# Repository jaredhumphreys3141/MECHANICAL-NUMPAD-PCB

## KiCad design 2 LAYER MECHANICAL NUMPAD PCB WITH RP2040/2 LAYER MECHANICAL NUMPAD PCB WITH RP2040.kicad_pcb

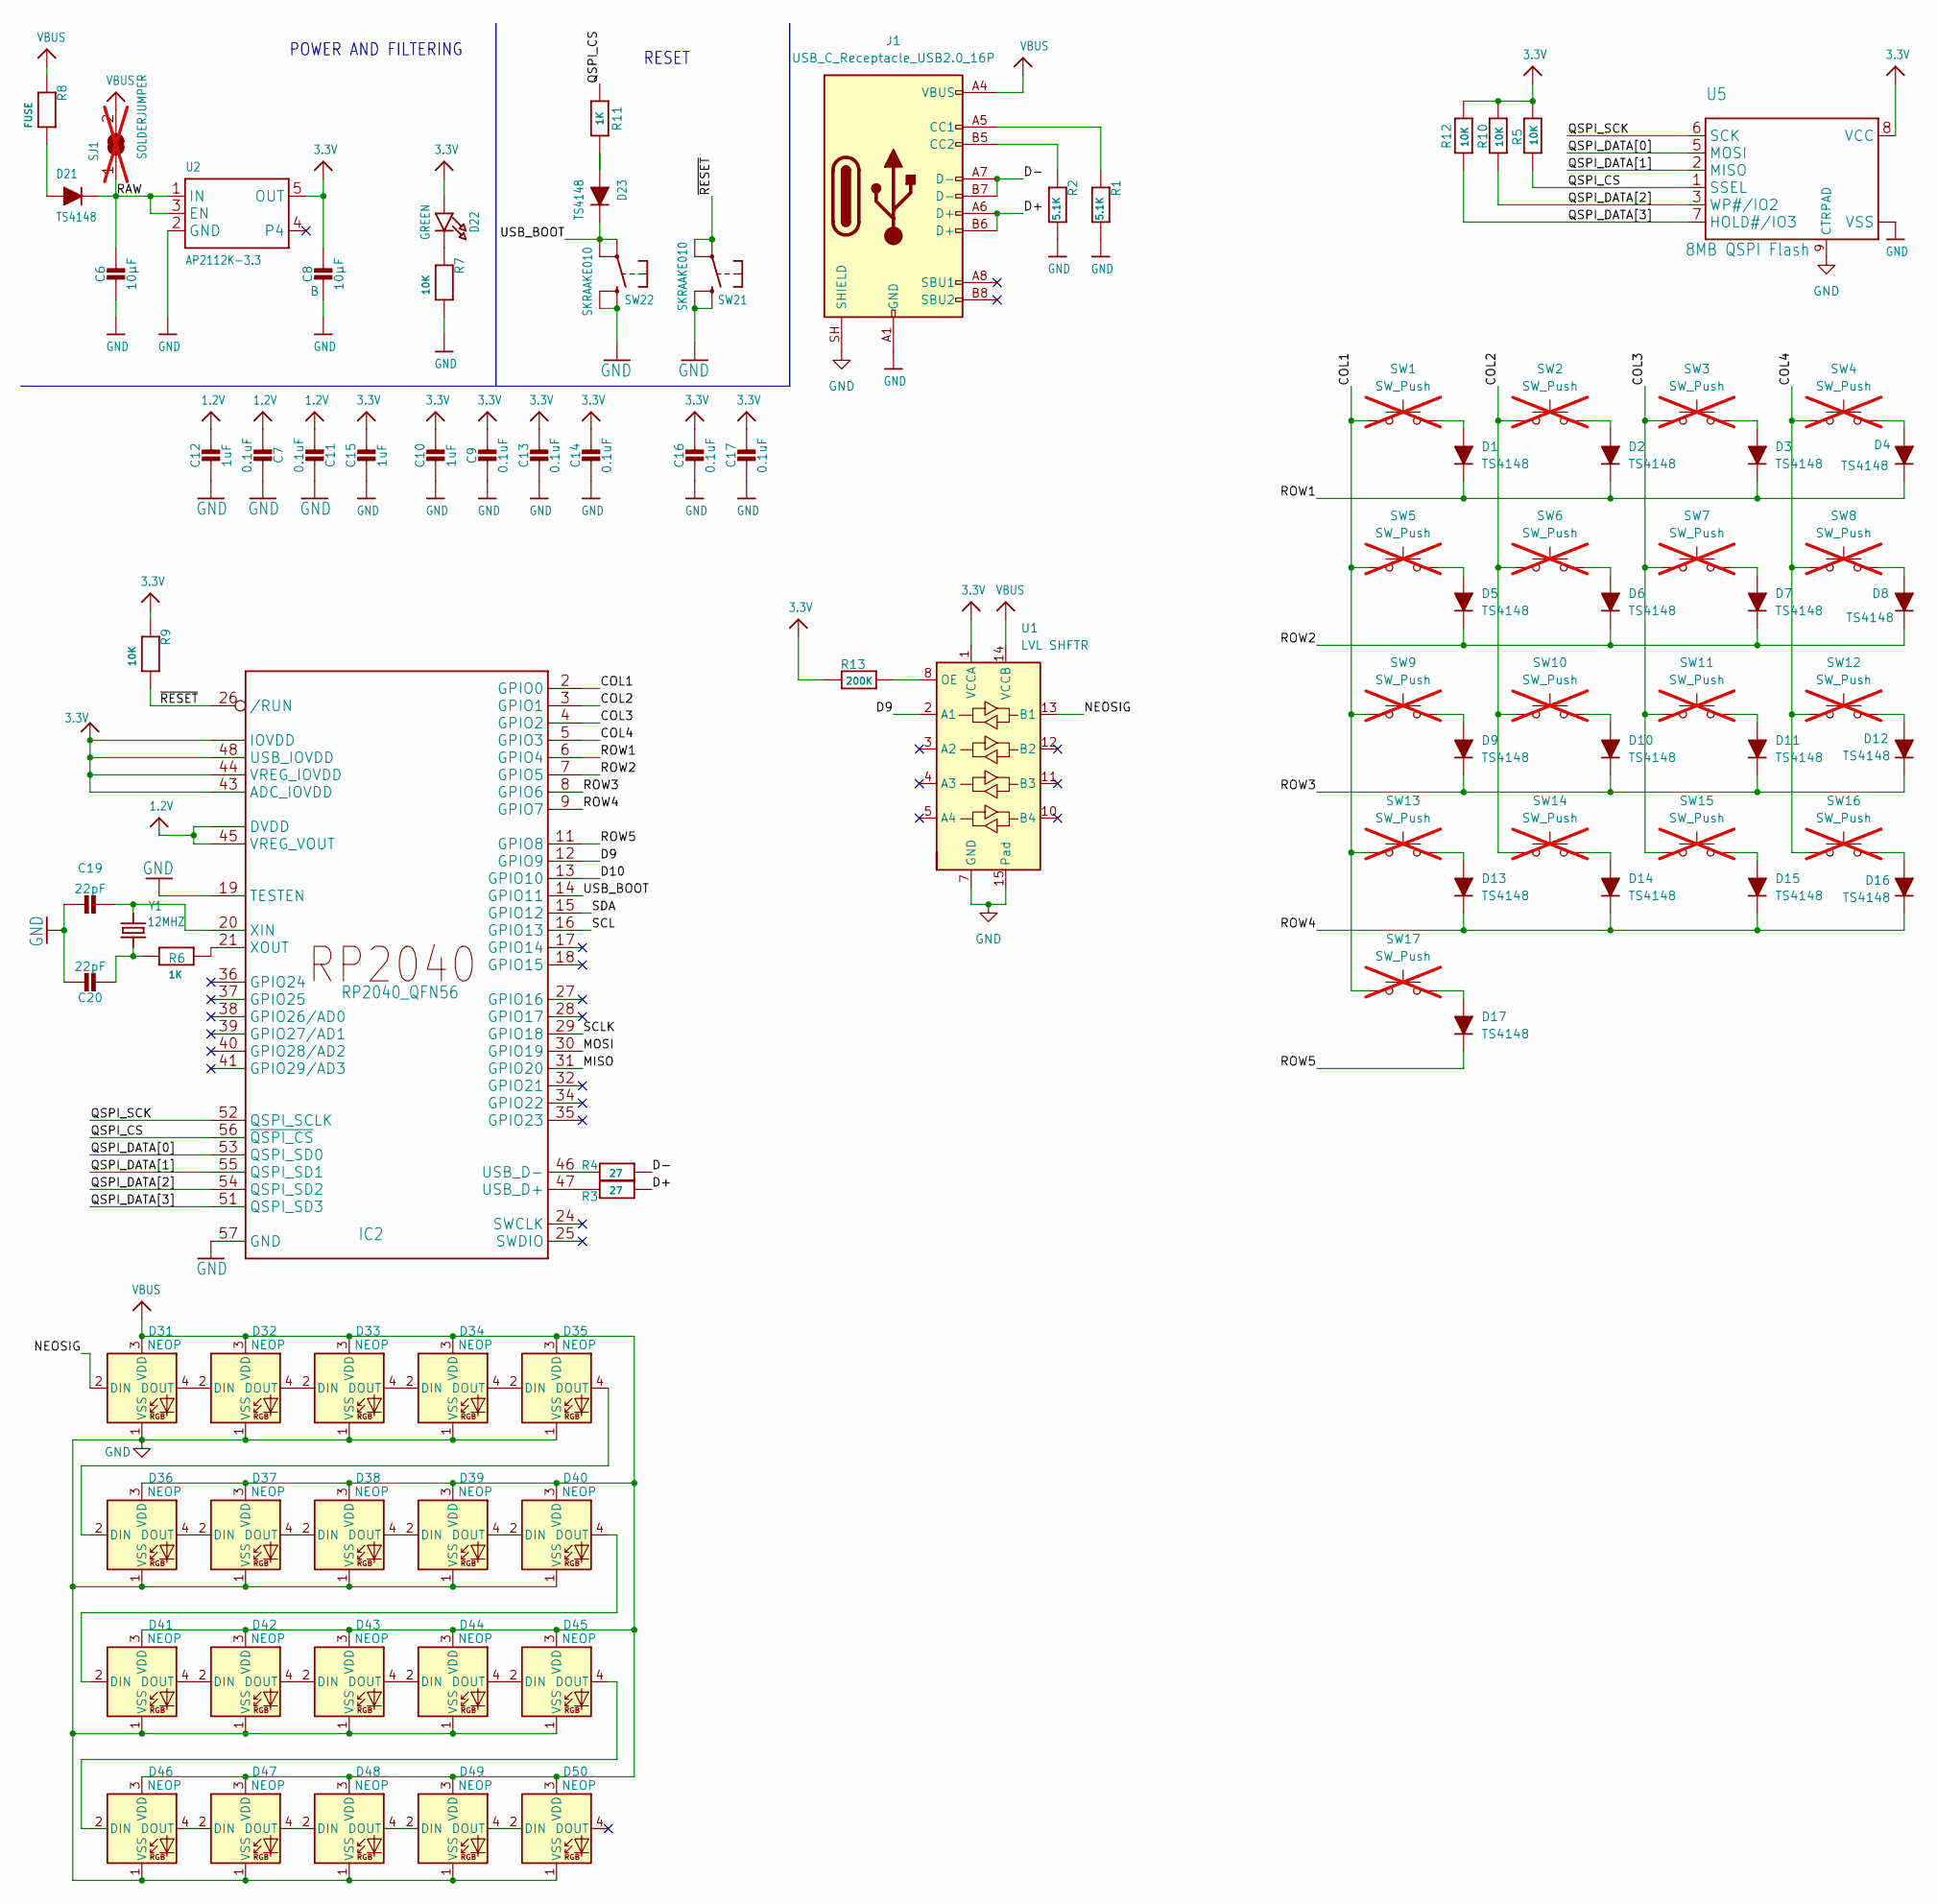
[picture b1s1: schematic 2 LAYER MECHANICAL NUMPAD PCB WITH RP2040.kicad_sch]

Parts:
C6, C8: 10µF; C_0603_1608Metric
C7, C9, C11, C13, C14, C16, C17: 0.1uF; C_0603_1608Metric
C10, C12, C15: 1uF; C_0603_1608Metric
C19, C20: 22pF; C_0603_1608Metric
D1, D2, D3, D4, D5, D6, D7, D8, D9, D10, D11, D12, D13, D14, D15, D16, D17, D21, D23: TS4148; D_0805_2012Metric
D22: GREEN; LED_0603_1608Metric_Green
D31, D32, D33, D34, D35, D36, D37, D38, D39, D40, D41, D42, D43, D44, D45, D46, D47, D48, D49, D50: NEOP; LED_SK6812MINI-E_3.2x2.8mm_P1.5mm_ReverseMount
IC2: RP2040_QFN56; QFN-56-1EP_7x7mm_P0.4mm_EP3.2x3.2mm
J1: USB_C_Receptacle_USB2.0_16P; USB_C_Receptacle_GCT_USB4105-xx-A_16P_TopMnt_Horizontal
R1, R2: 5.1K; R_0603_1608Metric
R3, R4: 27; R_0603_1608Metric
R5, R7, R9, R10, R12: 10K; R_0603_1608Metric
R6, R11: 1K; R_0603_1608Metric
R8: FUSE; Fuse_0603_1608Metric
R13: 200K; R_0603_1608Metric
SJ1: SOLDERJUMPER; SolderJumper-2_P1.3mm_Open_Pad1.0x1.5mm; not fitted
SW1, SW2, SW3, SW4, SW5, SW6, SW7, SW8, SW9, SW10, SW11, SW12, SW13, SW14, SW15, SW16, SW17: SW_Push; SW_Hotswap_Kailh_MX_1.00u; not fitted
SW21, SW22: SKRAAKE010; SW4_SKRAAKE010_ALPS
U1: LVL SHFTR; Texas_S-PVQFN-N14
U2: AP2112K-3.3; SOT23-5
U5: 8MB QSPI Flash; USON-8_3x2mm-SkinnyCenterPad
Y1: 12MHZ; Crystal_SMD_3215-2Pin_3.2x1.5mm

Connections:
1.2V: C7.2, C11.2, C12.1, IC2.23 (DVDD), IC2.45 (VREG_VOUT), IC2.50 (DVDD)
3.3V: C8.1, C9.1, C10.1, C13.1, C14.1, C15.1, C16.1, C17.1, D22.1 (A), IC2.1 (IOVDD), IC2.10 (IOVDD), IC2.22 (IOVDD), IC2.33 (IOVDD), IC2.42 (IOVDD), IC2.43 (ADC_IOVDD), IC2.44 (VREG_IOVDD), IC2.48 (USB_IOVDD), IC2.49 (IOVDD), R5.2, R9.1, R10.2, R12.2, R13.1, U1.1 (VCCA), U2.5 (OUT), U5.8 (VCC)
/COL1: IC2.2 (GPIO0), SW1.1, SW5.1, SW9.1, SW13.1, SW17.1
/COL2: IC2.3 (GPIO1), SW2.1, SW6.1, SW10.1, SW14.1
/COL3: IC2.4 (GPIO2), SW3.1, SW7.1, SW11.1, SW15.1
/COL4: IC2.5 (GPIO3), SW4.1, SW8.1, SW12.1, SW16.1
/D9: IC2.12 (GPIO9), U1.2 (A1)
/D10: IC2.13 (GPIO10)
/D+: J1.A6 (D+), J1.B6 (D+), R3.2
/D-: J1.A7 (D-), J1.B7 (D-), R4.2
/MISO: IC2.31 (GPIO20)
/MOSI: IC2.30 (GPIO19)
/NEOSIG: D31.2 (DIN), U1.13 (B1)
/QSPI_CS: IC2.56 (~QSPI_CS), R5.1, R11.1, U5.1 (SSEL)
/QSPI_DATA[0]: IC2.53 (QSPI_SD0), U5.5 (MOSI)
/QSPI_DATA[1]: IC2.55 (QSPI_SD1), U5.2 (MISO)
/QSPI_DATA[2]: IC2.54 (QSPI_SD2), R10.1, U5.3 (WP#/IO2)
/QSPI_DATA[3]: IC2.51 (QSPI_SD3), R12.1, U5.7 (HOLD#/IO3)
/QSPI_SCK: IC2.52 (QSPI_SCLK), U5.6 (SCK)
/RAW: C6.1, D21.1 (K), SJ1.1, U2.1 (IN), U2.3 (EN)
/ROW1: D1.1 (K), D2.1 (K), D3.1 (K), D4.1 (K), IC2.6 (GPIO4)
/ROW2: D5.1 (K), D6.1 (K), D7.1 (K), D8.1 (K), IC2.7 (GPIO5)
/ROW3: D9.1 (K), D10.1 (K), D11.1 (K), D12.1 (K), IC2.8 (GPIO6)
/ROW4: D13.1 (K), D14.1 (K), D15.1 (K), D16.1 (K), IC2.9 (GPIO7)
/ROW5: D17.1 (K), IC2.11 (GPIO8)
/SCL: IC2.16 (GPIO13)
/SCLK: IC2.29 (GPIO18)
/SDA: IC2.15 (GPIO12)
/USB_BOOT: D23.1 (K), IC2.14 (GPIO11), SW22.1, SW22.3 (P1)
/~RESET: IC2.26 (/RUN), R9.2, SW21.1, SW21.3 (P1)
GND: C6.2, C7.1, C8.2, C9.2, C10.2, C11.1, C12.2, C13.2, C14.2, C15.2, C16.2, C17.2, C19.1, C20.1, D31.1 (VSS), D32.1 (VSS), D33.1 (VSS), D34.1 (VSS), D35.1 (VSS), D36.1 (VSS), D37.1 (VSS), D38.1 (VSS), D39.1 (VSS), D40.1 (VSS), D41.1 (VSS), D42.1 (VSS), D43.1 (VSS), D44.1 (VSS), D45.1 (VSS), D46.1 (VSS), D47.1 (VSS), D48.1 (VSS), D49.1 (VSS), D50.1 (VSS), IC2.19 (TESTEN), IC2.57 (GND), J1.A1 (GND), J1.A12 (GND), J1.B1 (GND), J1.B12 (GND), J1.SH (SHIELD), R1.2, R2.2, R7.2, SW21.2 (S), SW21.4 (S1), SW22.2 (S), SW22.4 (S1), U1.7 (GND), U1.15 (Pad), U2.2 (GND), U5.4 (VSS), U5.9 (CTRPAD)
unnamed: C20.2, R6.1, Y1.1
unnamed: D1.2 (A), SW1.2
unnamed: D2.2 (A), SW2.2
unnamed: D3.2 (A), SW3.2
unnamed: D4.2 (A), SW4.2
unnamed: D5.2 (A), SW5.2
unnamed: D6.2 (A), SW6.2
unnamed: D7.2 (A), SW7.2
unnamed: D8.2 (A), SW8.2
unnamed: D9.2 (A), SW9.2
unnamed: D10.2 (A), SW10.2
unnamed: D11.2 (A), SW11.2
unnamed: D12.2 (A), SW12.2
unnamed: D13.2 (A), SW13.2
unnamed: D14.2 (A), SW14.2
unnamed: D15.2 (A), SW15.2
unnamed: D16.2 (A), SW16.2
unnamed: D17.2 (A), SW17.2
unnamed: D21.2 (A), R8.2
unnamed: D22.2 (C), R7.1
unnamed: D23.2 (A), R11.2
unnamed: D31.4 (DOUT), D32.2 (DIN)
unnamed: D32.4 (DOUT), D33.2 (DIN)
unnamed: D33.4 (DOUT), D34.2 (DIN)
unnamed: D34.4 (DOUT), D35.2 (DIN)
unnamed: D35.4 (DOUT), D36.2 (DIN)
unnamed: D36.4 (DOUT), D37.2 (DIN)
unnamed: D37.4 (DOUT), D38.2 (DIN)
unnamed: D38.4 (DOUT), D39.2 (DIN)
unnamed: D39.4 (DOUT), D40.2 (DIN)
unnamed: D40.4 (DOUT), D41.2 (DIN)
unnamed: D41.4 (DOUT), D42.2 (DIN)
unnamed: D42.4 (DOUT), D43.2 (DIN)
unnamed: D43.4 (DOUT), D44.2 (DIN)
unnamed: D44.4 (DOUT), D45.2 (DIN)
unnamed: D45.4 (DOUT), D46.2 (DIN)
unnamed: D46.4 (DOUT), D47.2 (DIN)
unnamed: D47.4 (DOUT), D48.2 (DIN)
unnamed: D48.4 (DOUT), D49.2 (DIN)
unnamed: D49.4 (DOUT), D50.2 (DIN)
unnamed: IC2.47 (USB_D+), R3.1
unnamed: IC2.46 (USB_D-), R4.1
unnamed: C19.2, IC2.20 (XIN), Y1.2
unnamed: IC2.21 (XOUT), R6.2
unnamed: J1.A5 (CC1), R1.1
unnamed: J1.B5 (CC2), R2.1
unnamed: R13.2, U1.8 (OE)
VBUS: D31.3 (VDD), D32.3 (VDD), D33.3 (VDD), D34.3 (VDD), D35.3 (VDD), D36.3 (VDD), D37.3 (VDD), D38.3 (VDD), D39.3 (VDD), D40.3 (VDD), D41.3 (VDD), D42.3 (VDD), D43.3 (VDD), D44.3 (VDD), D45.3 (VDD), D46.3 (VDD), D47.3 (VDD), D48.3 (VDD), D49.3 (VDD), D50.3 (VDD), J1.A4 (VBUS), J1.A9 (VBUS), J1.B4 (VBUS), J1.B9 (VBUS), R8.1, SJ1.2, U1.14 (VCCB)

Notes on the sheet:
RESET
POWER AND FILTERING

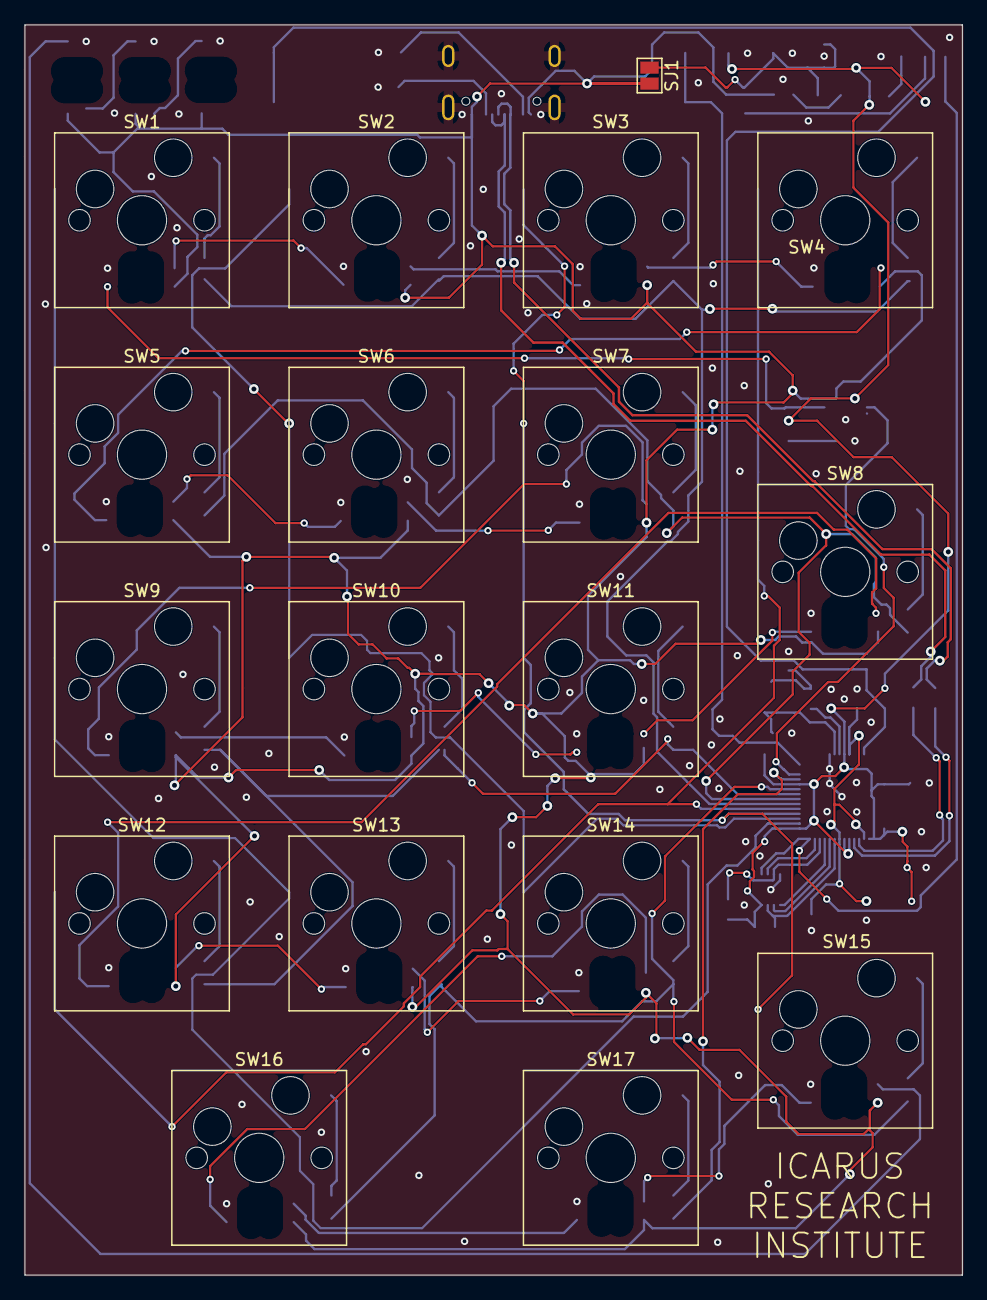
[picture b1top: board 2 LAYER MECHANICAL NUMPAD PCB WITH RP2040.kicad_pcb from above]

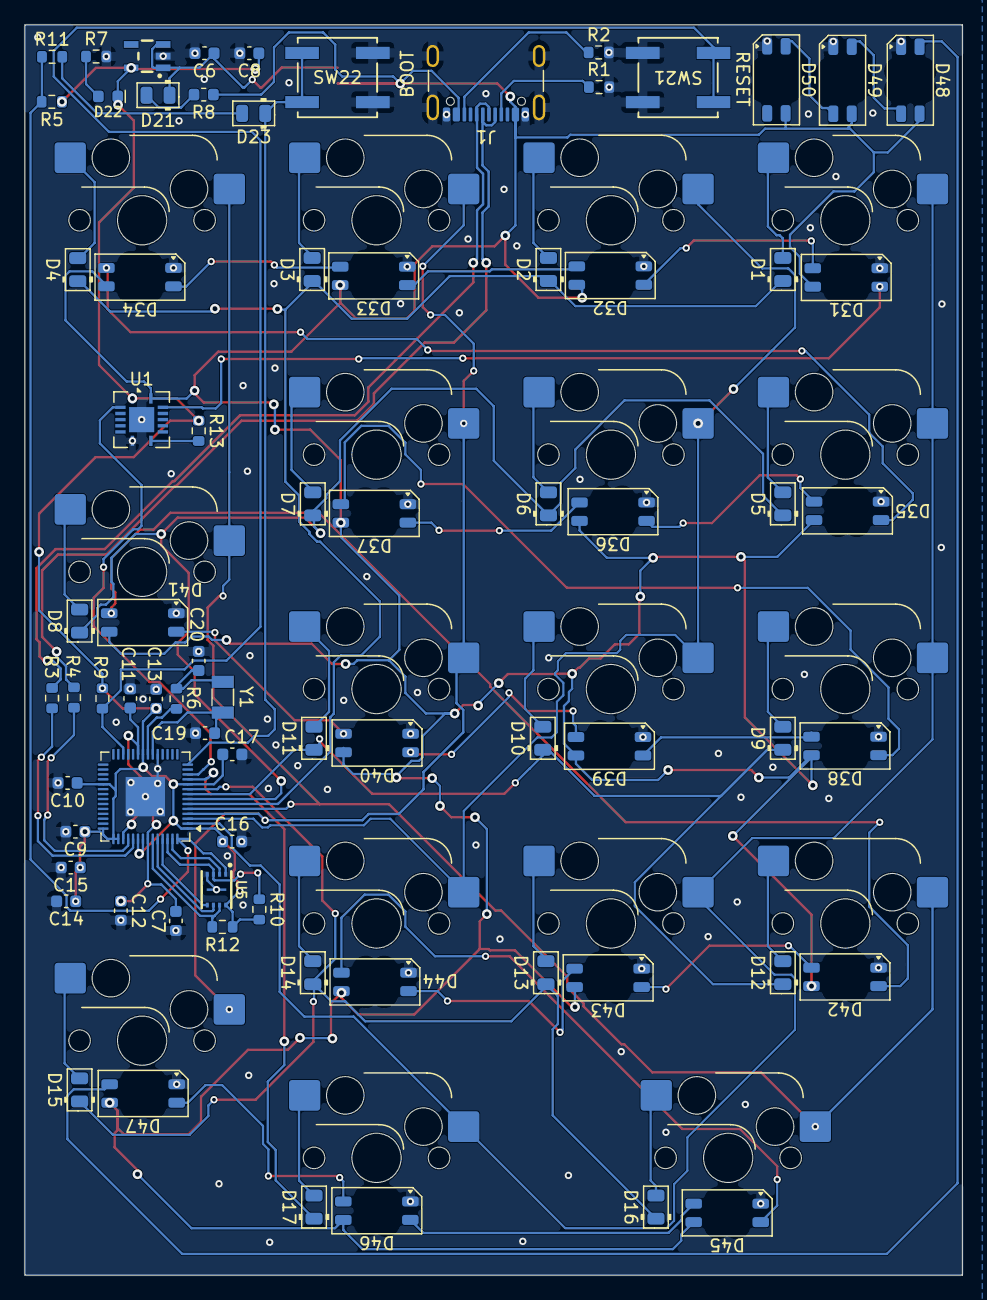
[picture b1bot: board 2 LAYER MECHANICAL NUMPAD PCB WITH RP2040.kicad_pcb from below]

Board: 2 copper layers, 76.2 x 101.6 mm, 93 parts (75 on the bottom side), 73 nets.

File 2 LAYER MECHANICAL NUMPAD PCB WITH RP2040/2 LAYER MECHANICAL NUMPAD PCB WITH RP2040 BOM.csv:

"Id";"Designator";"Footprint";"Quantity";"Designation";"Supplier and ref";
1;"C6, C8";"C_0603_1608Metric";2;"10µF";;;
2;"C7, C9, C11, C13, C14, C16, C17";"C_0603_1608Metric";7;"0.1uF";;;
3;"C10, C12, C15";"C_0603_1608Metric";3;"1uF";;;
4;"C19, C20";"C_0603_1608Metric";2;"22pF";;;
5;"D1, D2, D3, D4, D5, D6, D7, D8, D9, D10, D11, D12, D13, D14, D15, D16, D17, D21, D23";"D_0805_2012Metric";19;"TS4148";;;
6;"D22";"LED_0603_1608Metric_Green";1;"GREEN";;;
7;"D31, D32, D33, D34, D35, D36, D37, D38, D39, D40, D41, D42, D43, D44, D45, D46, D47, D48, D49, D50";"LED_SK6812MINI-E_3.2x2.8mm_P1.5mm_ReverseMount";20;"NEOP";;;
8;"IC2";"QFN-56-1EP_7x7mm_P0.4mm_EP3.2x3.2mm";1;"RP2040_QFN56";;;
9;"J1";"USB_C_Receptacle_GCT_USB4105-xx-A_16P_TopMnt_Horizontal";1;"USB_C_Receptacle_USB2.0_16P";;;
10;"R1, R2";"R_0603_1608Metric";2;"5.1K";;;
11;"R3, R4";"R_0603_1608Metric";2;"27";;;
12;"R5, R7, R9, R10, R12";"R_0603_1608Metric";5;"10K";;;
13;"R6, R11";"R_0603_1608Metric";2;"1K";;;
14;"R8";"Fuse_0603_1608Metric";1;"FUSE";;;
15;"R13";"R_0603_1608Metric";1;"200K";;;
16;"SW21, SW22";"SW4_SKRAAKE010_ALPS";2;"SKRAAKE010";;;
17;"U1";"Texas_S-PVQFN-N14";1;"LVL SHFTR";;;
18;"U2";"SOT23-5";1;"AP2112K-3.3";;;
19;"U5";"USON-8_3x2mm-SkinnyCenterPad";1;"8MB QSPI Flash";;;
20;"Y1";"Crystal_SMD_3215-2Pin_3.2x1.5mm";1;"12MHZ";;;

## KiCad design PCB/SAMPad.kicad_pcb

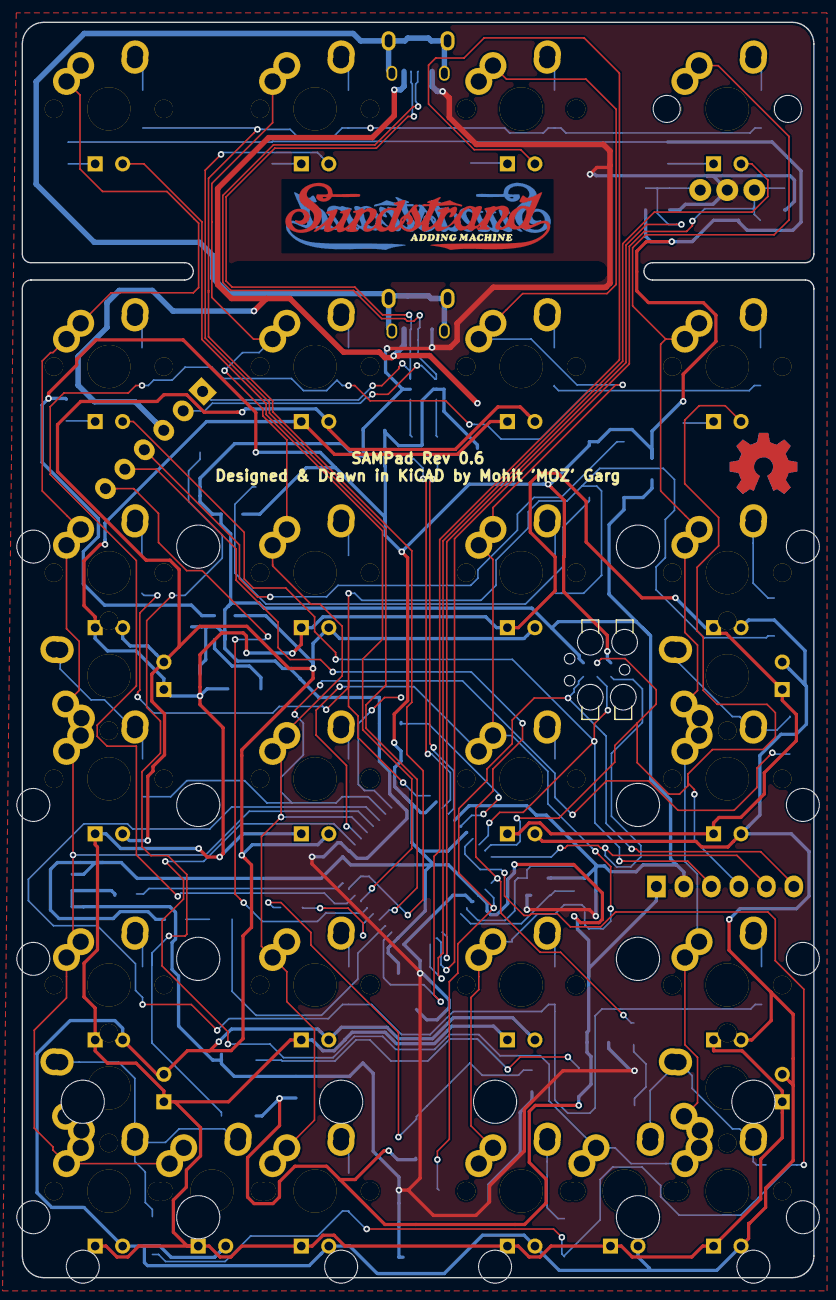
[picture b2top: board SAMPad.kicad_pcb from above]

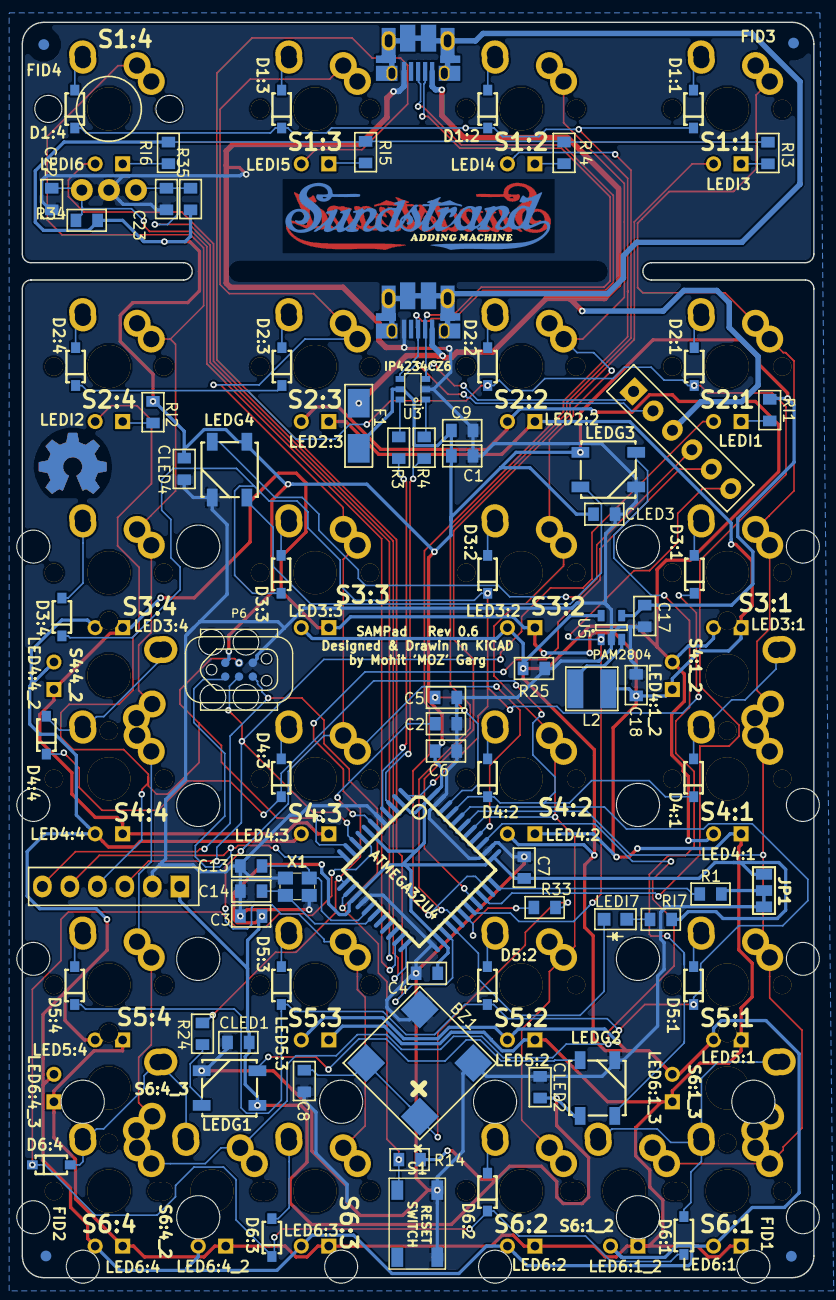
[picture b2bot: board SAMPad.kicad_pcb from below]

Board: 2 copper layers, 73.2 x 116.0 mm, 154 parts (85 on the bottom side), 79 nets.

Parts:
BZ1: BUZZER; BUZZER_SMT
C1, C2, C22, C23: 1uF; SMD_0805
C3, C4, C5, C6, C7, C8: 0.1uF; SMD_0805
C9, C17, C18: 10uF; SMD_0805
C13, C14: 8pF; SMD_0805
CLED1, CLED2, CLED3, CLED4: 0.1 uF; SMD_0805
D1:1, D1:2, D1:3, D1:4, D2:1, D2:2, D2:3, D2:4, D3:1, D3:2, D3:3, D3:4, D4:1, D4:2, D4:3, D4:4, D5:1, D5:2, D5:3, D5:4, D6:1, D6:2, D6:3, D6:4: DIODE; SOD123-DIODE
F1: PTC FUSE; Fuse_SMD1206
FID1, FID2, FID3, FID4: MISC; FID
HOLE1: MISC; FID
JP1: JUMPER; JUMPER_SMD_3
L2: 4.7uH; Inductor_Bourn_4mmx4mm
LED2:2, LED2:3, LED3:1, LED3:2, LED3:3, LED3:4, LED4:1, LED4:1_2, LED4:2, LED4:3, LED4:4, LED4:4_2, LED5:1, LED5:2, LED5:3, LED5:4, LED6:1, LED6:1_2, LED6:1_3, LED6:2, LED6:3, LED6:4, LED6:4_2, LED6:4_3: LED; INSW_LEDS_REG
LEDG1, LEDG2, LEDG3, LEDG4: WS2812B
LEDI1, LEDI2, LEDI3, LEDI4, LEDI5, LEDI6: LED; INSW_LEDS_REG
LEDI7: LED; LED_0805
LOGO1, LOGO2: MISC; SAMPad-Logo
LOGO3, LOGO4: MISC; OSHW
P1, P1_2: USB_CONN; USB_Micro-B
P4, P5: CONN_6; Pin_Header_1x06
P6: ISP6; TC2030_BIG
R1, R34, R35: 10k; SMD_0805
R3, R4: 22; SMD_0805
R14: 100k; SMD_0805
R24: 330; SMD_0805
R25: RLED; SMD_0805
R33: 100; SMD_0805
RI1, RI2, RI3, RI4, RI5, RI6, RI7: 470; SMD_0805
S1: TAC_SWITCH; TACT_5.2x5.2
S1:1, S1:2, S1:3, S1:4, S2:1, S2:2, S2:3, S2:4, S3:1, S3:2, S3:3, S3:4, S4:1, S4:1_2, S4:2, S4:3, S4:4, S4:4_2, S5:1, S5:2, S5:3, S5:4, S6:1, S6:1_2, S6:1_3, S6:2, S6:3, S6:4, S6:4_2, S6:4_3: SW; MXALPS2
S2: ENCODER; ENCODER_12MM
STAB1, STAB2, STAB3, STAB4, STAB5, STAB6: MISC; MX_200
U1: ATMEGA32U4; TQFP44
U3: IP4234CZ6; SOT457
U5: PAM2804; SOT-23-5
X1: CRYSTAL; NX3225SA

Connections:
+5V: C1.1, C3.1, C4.1, C6.1, C7.1, C9.1, C17.1, CLED1.2, CLED2.2, CLED3.1, CLED4.1, F1.2, JP1.1, LEDG1.1, LEDG2.1, LEDG3.1, LEDG4.1, P5.1, P6.2, R14.2, R34.2, R35.1, RI1.2, RI2.2, RI3.2, RI4.2, RI5.2, RI6.2, RI7.2, U1.2, U1.7, U1.14, U1.24, U1.34, U1.44, U3.5, U5.4
/ledmatrix/LEDAN: C18.1, L2.2, LED2:2.1, LED2:3.1, LED3:1.1, LED3:2.1, LED3:3.1, LED3:4.1, LED4:1.1, LED4:1_2.1, LED4:2.1, LED4:3.1, LED4:4.1, LED4:4_2.1, LED5:1.1, LED5:2.1, LED5:3.1, LED5:4.1, LED6:1.1, LED6:1_2.1, LED6:1_3.1, LED6:2.1, LED6:3.1, LED6:4.1, LED6:4_2.1, LED6:4_3.1
/ledmatrix/LEDCATH: LED2:2.2, LED2:3.2, LED3:1.2, LED3:2.2, LED3:3.2, LED3:4.2, LED4:1.2, LED4:1_2.2, LED4:2.2, LED4:3.2, LED4:4.2, LED4:4_2.2, LED5:1.2, LED5:2.2, LED5:3.2, LED5:4.2, LED6:1.2, LED6:1_2.2, LED6:1_3.2, LED6:2.2, LED6:3.2, LED6:4.2, LED6:4_2.2, LED6:4_3.2, R25.2, U5.5
/ledmatrix/LEDI1: LEDI1.2, P5.3, P6.3, U1.9
/ledmatrix/LEDI2: LEDI2.2, P5.4, P6.4, U1.10
/ledmatrix/LEDI3: LEDI3.2, U1.30
/ledmatrix/LEDI4: LEDI4.2, U1.27
/ledmatrix/LEDI5: LEDI5.2, U1.25
/ledmatrix/LEDI6: LEDI6.2, U1.22
/ledmatrix/LEDI7: LEDI7.2, U1.26
/ledmatrix/RGBDIN: P4.5, R24.2, U1.12
/ledmatrix/RGBDOUT: LEDG4.2, P4.4
/mcu/BUZZER: R33.1, U1.28
/mcu/COL1: S1:1.1, S2:1.1, S3:1.1, S4:1.1, S4:1_2.1, S5:1.1, S6:1.1, S6:1_2.1, S6:1_3.1, U1.39
/mcu/COL2: S1:2.1, S2:2.1, S3:2.1, S4:2.1, S5:2.1, S6:2.1, U1.38
/mcu/COL3: S1:3.1, S2:3.1, S3:3.1, S4:3.1, S5:3.1, S6:3.1, U1.37
/mcu/COL4: S1:4.1, S2:4.1, S3:4.1, S4:4.1, S4:4_2.1, S5:4.1, S6:4.1, S6:4_2.1, S6:4_3.1, U1.36
/mcu/D+: P1.3, P1_2.3, P4.2, U3.4
/mcu/D-: P1.2, P1_2.2, P4.1, U3.3
/mcu/ENCA: C22.1, R34.1, S2.1, U1.21
/mcu/ENCB: C23.1, R35.2, S2.3, U1.20
/mcu/HWBE: R1.2, U1.33
/mcu/LEDBL: P4.6, U1.29, U5.1
/mcu/MCURST: P5.6, P6.5, R14.1, S1.2, U1.13
/mcu/MISO: P5.5, P6.1, U1.11
/mcu/ROW1: D1:1.2, D1:2.2, D1:3.2, D1:4.2, U1.32
/mcu/ROW2: D2:1.2, D2:2.2, D2:3.2, D2:4.2, U1.31
/mcu/ROW3: D3:1.2, D3:2.2, D3:3.2, D3:4.2, U1.1
/mcu/ROW4: D4:1.2, D4:2.2, D4:3.2, D4:4.2, U1.41
/mcu/ROW5: D5:1.2, D5:2.2, D5:3.2, D5:4.2, U1.40
/mcu/ROW6: D6:1.2, D6:2.2, D6:3.2, D6:4.2, U1.8
/mcu/SHDGND: P1.6, P1_2.6
/mcu/USB_D+: R3.2, U1.4
/mcu/USB_D-: R4.2, U1.3
/mcu/VUSB: F1.1, P1.1, P1_2.1, P4.3
/mcu/XTAL1: C14.1, U1.17, X1.3
/mcu/XTAL2: C13.1, U1.16, X1.1
unnamed: BZ1.1, C8.2, R33.2
unnamed: C2.1, U1.6
unnamed: C5.1, U1.42
unnamed: D1:1.1, S1:1.2
unnamed: D1:2.1, S1:2.2
unnamed: D1:3.1, S1:3.2
unnamed: D1:4.1, S1:4.2
unnamed: D2:1.1, S2:1.2
unnamed: D2:2.1, S2:2.2
unnamed: D2:3.1, S2:3.2
unnamed: D2:4.1, S2:4.2
unnamed: D3:1.1, S3:1.2
unnamed: D3:2.1, S3:2.2
unnamed: D3:3.1, S3:3.2
unnamed: D3:4.1, S3:4.2
unnamed: D4:1.1, S4:1.2, S4:1_2.2
unnamed: D4:2.1, S4:2.2
unnamed: D4:3.1, S4:3.2
unnamed: D4:4.1, S4:4.2, S4:4_2.2
unnamed: D5:1.1, S5:1.2
unnamed: D5:2.1, S5:2.2
unnamed: D5:3.1, S5:3.2
unnamed: D5:4.1, S5:4.2
unnamed: D6:1.1, S6:1.2, S6:1_2.2, S6:1_3.2
unnamed: D6:2.1, S6:2.2
unnamed: D6:3.1, S6:3.2
unnamed: D6:4.1, S6:4.2, S6:4_2.2, S6:4_3.2
unnamed: L2.1, U5.3
unnamed: LEDG1.2, LEDG2.4
unnamed: LEDG1.4, R24.1
unnamed: LEDG2.2, LEDG3.4
unnamed: LEDG3.2, LEDG4.4
unnamed: LEDI1.1, RI1.1
unnamed: LEDI2.1, RI2.1
unnamed: LEDI3.1, RI3.1
unnamed: LEDI4.1, RI4.1
unnamed: LEDI5.1, RI5.1
unnamed: LEDI6.1, RI6.1
unnamed: LEDI7.1, RI7.1
unnamed: R3.1, U3.6
unnamed: R4.1, U3.1
VSS: BZ1.2, C1.2, C2.2, C3.2, C4.2, C5.2, C6.2, C7.2, C8.1, C9.2, C13.2, C14.2, C17.2, C18.2, C22.2, C23.2, CLED1.1, CLED2.1, CLED3.2, CLED4.2, JP1.2, JP1.3, LEDG1.3, LEDG2.3, LEDG3.3, LEDG4.3, P1.5, P1_2.5, P5.2, P6.6, R1.1, R25.1, S1.3, S1.4, S2.2, U1.5, U1.15, U1.23, U1.35, U1.43, U3.2, U5.2, X1.2, X1.4

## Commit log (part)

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2026-06-12 Copied over files
2026-06-14 Added footprints
    Assigned footprints to all components, learned about bulk schematic symbol editing
2026-06-14 Connecting components by matching symbol pin and footprint pad labels
2026-06-15 Refinement of schematic and PCB
2026-06-16 Finished PCB
2026-06-16 In progress of adding Neopixels
2026-06-18 Generating Gerbers and refining PCBs
2026-06-19 Created new 2 layer board
2026-06-20 Created files
2026-06-22 Finalized PCB design
2026-06-22 Closed KiCAD
2026-06-22 Opened files
2026-06-22 Created BOM
2026-06-24 Finalized PCB and ordered 3X PCBs, 1X solder stencil, solder paste, and various components
